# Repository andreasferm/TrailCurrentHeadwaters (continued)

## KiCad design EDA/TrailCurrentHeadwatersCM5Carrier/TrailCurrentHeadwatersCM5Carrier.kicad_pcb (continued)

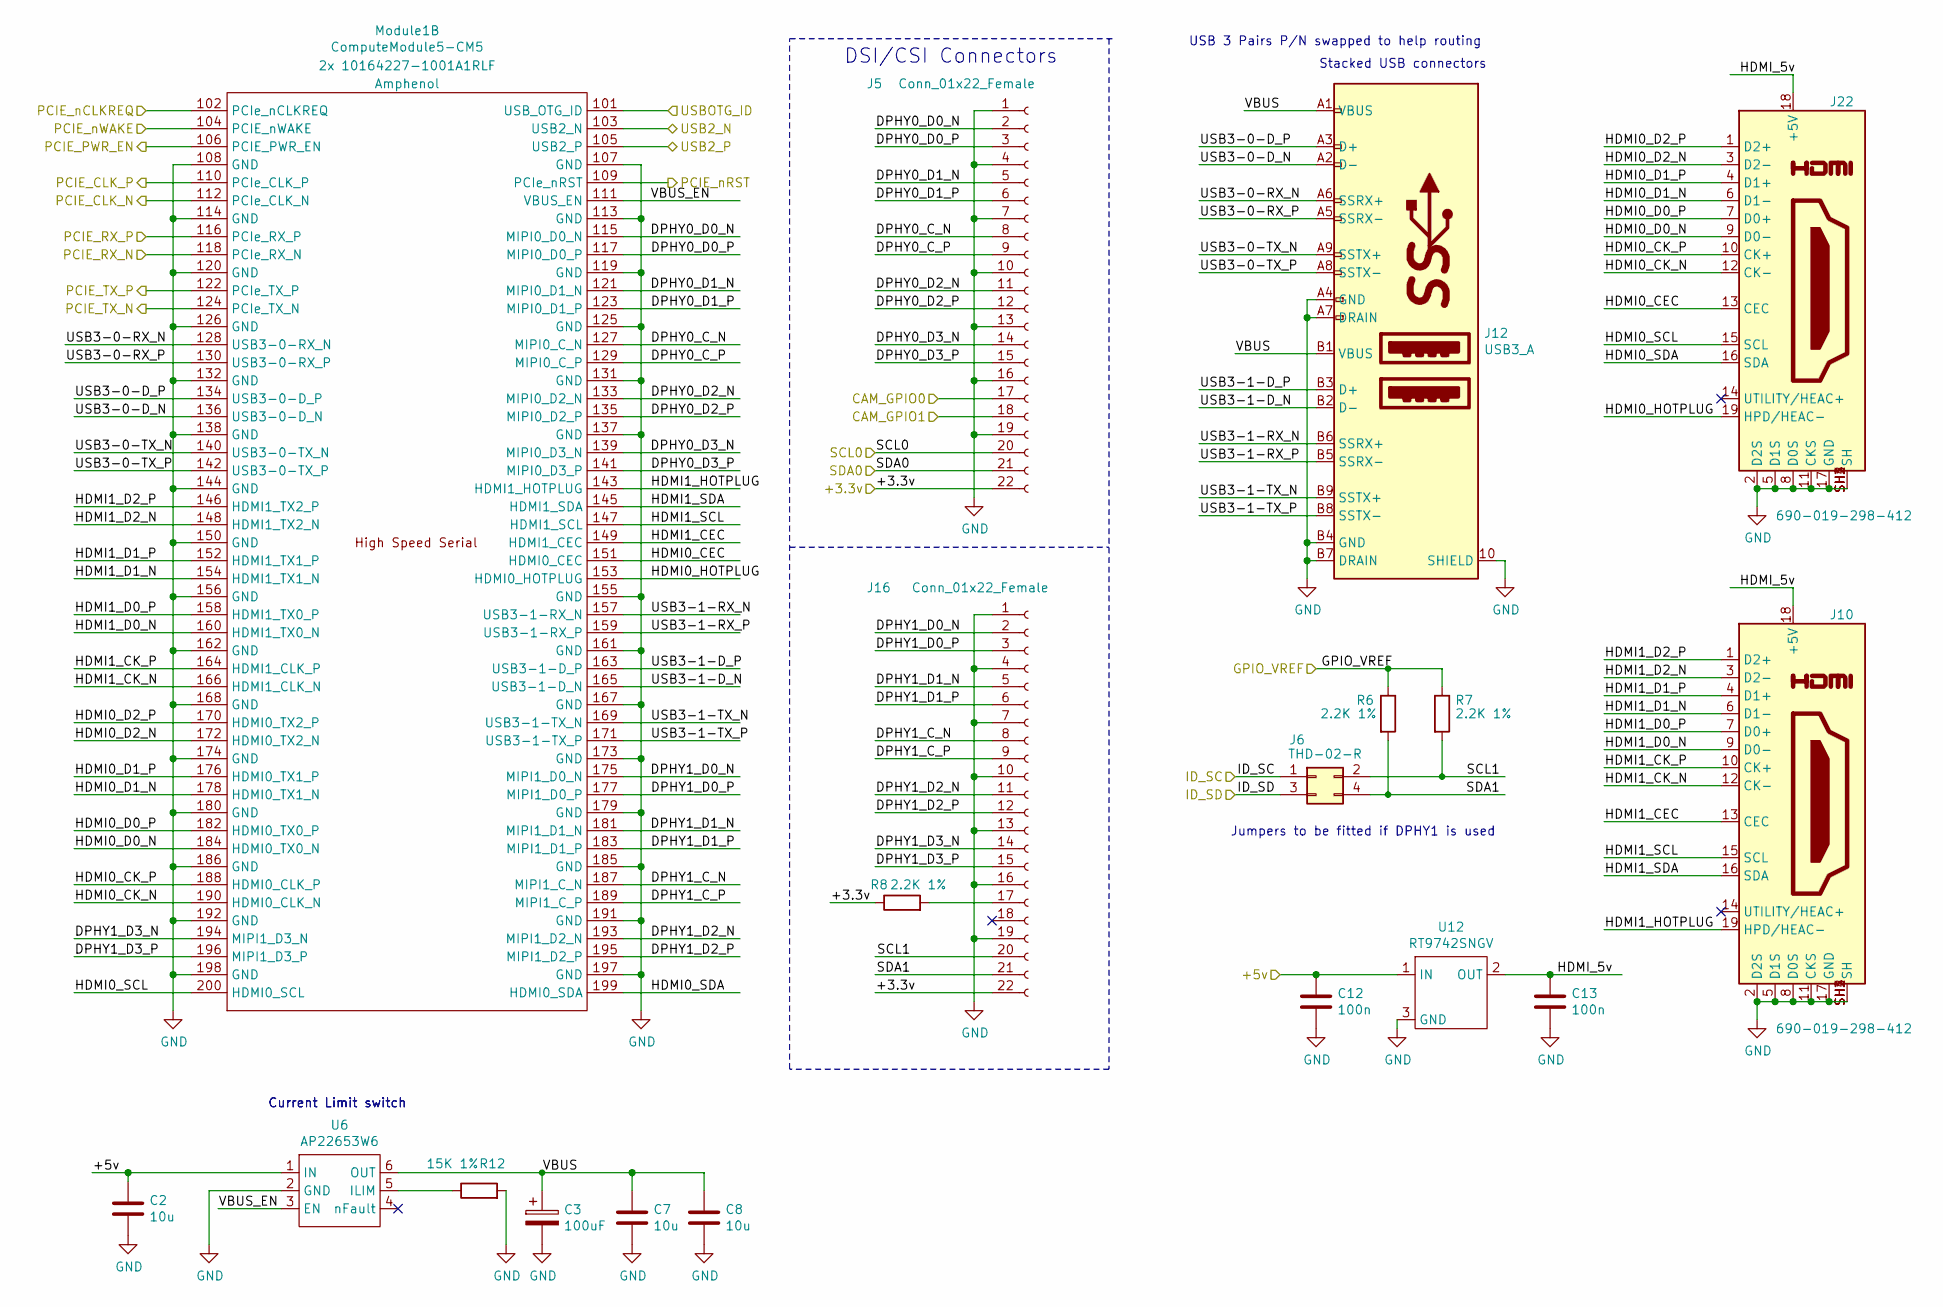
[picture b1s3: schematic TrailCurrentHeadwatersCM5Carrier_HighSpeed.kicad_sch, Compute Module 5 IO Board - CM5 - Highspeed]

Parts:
C2, C7, C8: 10u; C_0805_2012Metric; Part Description 10uF 10% 10V Ceramic Capacitor X7R 0805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
C3: 100uF; CP_EIA-7343-31_Kemet-D; Part Description Capacitor, SP-Cap, 100u, 6.3V, 15mR ESR
C12, C13: 100n; C_0402_1005Metric; Part Description 0.1uF 10% 16V Ceramic Capacitor X7R 040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
J5, J16: Conn_01x22_Female; Hirose_FH12-22S-0.5SH_1x22-1MP_P0.50mm_Horizontal; Part Description 22 Position FFC, FPC Connector Contacts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
J6: THD-02-R; PinHeader_2x02_P2.54mm_Vertical; Part Description PinHeader_2x02_P2.54mm_Vertical
J10, J22: 690-019-298-412; EDAC 690-019-298-412; Part Description HDMI Connector, Right Angle, 19 Contact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
J12: USB3_A; MTCONN_UBAF30-D2011; Part Description Dual USB 3 connector
Module1: ComputeModule5-CM5; Raspberry-Pi-5-Compute-Module; Part Description 100 Position Connector Receptacle, Cent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
R6, R7, R8: 2.2K 1%; R_0402_1005Metric; Part Description Resistor 2.2K M1005 1% 63mW
R12: 15K 1%; R_0402_1005Metric; Part Description Resistor 15K M1005 1% 63mW
U6: AP22653W6; SOT-23-6; Part Description Power Switch/Driver 1:1 P-Channel 2.1A 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
U12: RT9742SNGV; TSOT-23_HandSoldering; Part Description Power Switch/Driver 1:1 N-Channel 500mA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

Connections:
/+3.3v: J5.22, J16.22, R8.1; also elsewhere on the board
/+5v: C2.1, C12.1, U6.1 (IN), U12.1 (IN); also elsewhere on the board
/TrailCurrentHeadwatersCM5Carrier_GPIO/CAM_GPIO0: J5.17; also elsewhere on the board
/TrailCurrentHeadwatersCM5Carrier_GPIO/CAM_GPIO1: J5.18; also elsewhere on the board
/TrailCurrentHeadwatersCM5Carrier_GPIO/GPIO_VREF: R6.1, R7.1; also elsewhere on the board
/TrailCurrentHeadwatersCM5Carrier_GPIO/ID_SC: J6.1; also elsewhere on the board
/TrailCurrentHeadwatersCM5Carrier_GPIO/ID_SD: J6.3; also elsewhere on the board
/TrailCurrentHeadwatersCM5Carrier_GPIO/USBOTG: Module1.101 (USB_OTG_ID); also elsewhere on the board
/TrailCurrentHeadwatersCM5Carrier_HighSpeed/DPHY0_C_N: J5.8, Module1.127 (MIPI0_C_N)
/TrailCurrentHeadwatersCM5Carrier_HighSpeed/DPHY0_C_P: J5.9, Module1.129 (MIPI0_C_P)
/TrailCurrentHeadwatersCM5Carrier_HighSpeed/DPHY0_D0_N: J5.2, Module1.115 (MIPI0_D0_N)
/TrailCurrentHeadwatersCM5Carrier_HighSpeed/DPHY0_D0_P: J5.3, Module1.117 (MIPI0_D0_P)
/TrailCurrentHeadwatersCM5Carrier_HighSpeed/DPHY0_D1_N: J5.5, Module1.121 (MIPI0_D1_N)
/TrailCurrentHeadwatersCM5Carrier_HighSpeed/DPHY0_D1_P: J5.6, Module1.123 (MIPI0_D1_P)
/TrailCurrentHeadwatersCM5Carrier_HighSpeed/DPHY0_D2_N: J5.11, Module1.133 (MIPI0_D2_N)
/TrailCurrentHeadwatersCM5Carrier_HighSpeed/DPHY0_D2_P: J5.12, Module1.135 (MIPI0_D2_P)
/TrailCurrentHeadwatersCM5Carrier_HighSpeed/DPHY0_D3_N: J5.14, Module1.139 (MIPI0_D3_N)
/TrailCurrentHeadwatersCM5Carrier_HighSpeed/DPHY0_D3_P: J5.15, Module1.141 (MIPI0_D3_P)
/TrailCurrentHeadwatersCM5Carrier_HighSpeed/DPHY1_C_N: J16.8, Module1.187 (MIPI1_C_N)
/TrailCurrentHeadwatersCM5Carrier_HighSpeed/DPHY1_C_P: J16.9, Module1.189 (MIPI1_C_P)
/TrailCurrentHeadwatersCM5Carrier_HighSpeed/DPHY1_D0_N: J16.2, Module1.175 (MIPI1_D0_N)
/TrailCurrentHeadwatersCM5Carrier_HighSpeed/DPHY1_D0_P: J16.3, Module1.177 (MIPI1_D0_P)
/TrailCurrentHeadwatersCM5Carrier_HighSpeed/DPHY1_D1_N: J16.5, Module1.181 (MIPI1_D1_N)
/TrailCurrentHeadwatersCM5Carrier_HighSpeed/DPHY1_D1_P: J16.6, Module1.183 (MIPI1_D1_P)
/TrailCurrentHeadwatersCM5Carrier_HighSpeed/DPHY1_D2_N: J16.11, Module1.193 (MIPI1_D2_N)
/TrailCurrentHeadwatersCM5Carrier_HighSpeed/DPHY1_D2_P: J16.12, Module1.195 (MIPI1_D2_P)
/TrailCurrentHeadwatersCM5Carrier_HighSpeed/DPHY1_D3_N: J16.14, Module1.194 (MIPI1_D3_N)
/TrailCurrentHeadwatersCM5Carrier_HighSpeed/DPHY1_D3_P: J16.15, Module1.196 (MIPI1_D3_P)
/TrailCurrentHeadwatersCM5Carrier_HighSpeed/HDMI0_CEC: J22.13 (CEC), Module1.151 (HDMI0_CEC)
/TrailCurrentHeadwatersCM5Carrier_HighSpeed/HDMI0_CK_N: J22.12 (CK-), Module1.190 (HDMI0_CLK_N)
/TrailCurrentHeadwatersCM5Carrier_HighSpeed/HDMI0_CK_P: J22.10 (CK+), Module1.188 (HDMI0_CLK_P)
/TrailCurrentHeadwatersCM5Carrier_HighSpeed/HDMI0_D0_N: J22.9 (D0-), Module1.184 (HDMI0_TX0_N)
/TrailCurrentHeadwatersCM5Carrier_HighSpeed/HDMI0_D0_P: J22.7 (D0+), Module1.182 (HDMI0_TX0_P)
/TrailCurrentHeadwatersCM5Carrier_HighSpeed/HDMI0_D1_N: J22.6 (D1-), Module1.178 (HDMI0_TX1_N)
/TrailCurrentHeadwatersCM5Carrier_HighSpeed/HDMI0_D1_P: J22.4 (D1+), Module1.176 (HDMI0_TX1_P)
/TrailCurrentHeadwatersCM5Carrier_HighSpeed/HDMI0_D2_N: J22.3 (D2-), Module1.172 (HDMI0_TX2_N)
/TrailCurrentHeadwatersCM5Carrier_HighSpeed/HDMI0_D2_P: J22.1 (D2+), Module1.170 (HDMI0_TX2_P)
/TrailCurrentHeadwatersCM5Carrier_HighSpeed/HDMI0_HOTPLUG: J22.19 (HPD/HEAC-), Module1.153 (HDMI0_HOTPLUG)
/TrailCurrentHeadwatersCM5Carrier_HighSpeed/HDMI0_SCL: J22.15 (SCL), Module1.200 (HDMI0_SCL)
/TrailCurrentHeadwatersCM5Carrier_HighSpeed/HDMI0_SDA: J22.16 (SDA), Module1.199 (HDMI0_SDA)
/TrailCurrentHeadwatersCM5Carrier_HighSpeed/HDMI1_CEC: J10.13 (CEC), Module1.149 (HDMI1_CEC)
/TrailCurrentHeadwatersCM5Carrier_HighSpeed/HDMI1_CK_N: J10.12 (CK-), Module1.166 (HDMI1_CLK_N)
/TrailCurrentHeadwatersCM5Carrier_HighSpeed/HDMI1_CK_P: J10.10 (CK+), Module1.164 (HDMI1_CLK_P)
/TrailCurrentHeadwatersCM5Carrier_HighSpeed/HDMI1_D0_N: J10.9 (D0-), Module1.160 (HDMI1_TX0_N)
/TrailCurrentHeadwatersCM5Carrier_HighSpeed/HDMI1_D0_P: J10.7 (D0+), Module1.158 (HDMI1_TX0_P)
/TrailCurrentHeadwatersCM5Carrier_HighSpeed/HDMI1_D1_N: J10.6 (D1-), Module1.154 (HDMI1_TX1_N)
/TrailCurrentHeadwatersCM5Carrier_HighSpeed/HDMI1_D1_P: J10.4 (D1+), Module1.152 (HDMI1_TX1_P)
/TrailCurrentHeadwatersCM5Carrier_HighSpeed/HDMI1_D2_N: J10.3 (D2-), Module1.148 (HDMI1_TX2_N)
/TrailCurrentHeadwatersCM5Carrier_HighSpeed/HDMI1_D2_P: J10.1 (D2+), Module1.146 (HDMI1_TX2_P)
/TrailCurrentHeadwatersCM5Carrier_HighSpeed/HDMI1_HOTPLUG: J10.19 (HPD/HEAC-), Module1.143 (HDMI1_HOTPLUG)
/TrailCurrentHeadwatersCM5Carrier_HighSpeed/HDMI1_SCL: J10.15 (SCL), Module1.147 (HDMI1_SCL)
/TrailCurrentHeadwatersCM5Carrier_HighSpeed/HDMI1_SDA: J10.16 (SDA), Module1.145 (HDMI1_SDA)
/TrailCurrentHeadwatersCM5Carrier_HighSpeed/HDMI_5v: C13.1, J10.18 (+5V), J22.18 (+5V), U12.2 (OUT)
/TrailCurrentHeadwatersCM5Carrier_HighSpeed/PCIE_CLK_N: Module1.112 (PCIe_CLK_N); also elsewhere on the board
/TrailCurrentHeadwatersCM5Carrier_HighSpeed/PCIE_CLK_P: Module1.110 (PCIe_CLK_P); also elsewhere on the board
/TrailCurrentHeadwatersCM5Carrier_HighSpeed/PCIE_PWR_EN: Module1.106 (PCIE_PWR_EN); also elsewhere on the board
/TrailCurrentHeadwatersCM5Carrier_HighSpeed/PCIE_RX_N: Module1.118 (PCIe_RX_N); also elsewhere on the board
/TrailCurrentHeadwatersCM5Carrier_HighSpeed/PCIE_RX_P: Module1.116 (PCIe_RX_P); also elsewhere on the board
/TrailCurrentHeadwatersCM5Carrier_HighSpeed/PCIE_TX_N: Module1.124 (PCIe_TX_N); also elsewhere on the board
/TrailCurrentHeadwatersCM5Carrier_HighSpeed/PCIE_TX_P: Module1.122 (PCIe_TX_P); also elsewhere on the board
/TrailCurrentHeadwatersCM5Carrier_HighSpeed/PCIE_nCLKREQ: Module1.102 (PCIe_nCLKREQ); also elsewhere on the board
/TrailCurrentHeadwatersCM5Carrier_HighSpeed/PCIE_nRST: Module1.109 (PCIe_nRST); also elsewhere on the board
/TrailCurrentHeadwatersCM5Carrier_HighSpeed/PCIE_nWAKE: Module1.104 (PCIE_nWAKE); also elsewhere on the board
/TrailCurrentHeadwatersCM5Carrier_HighSpeed/SCL0: J5.20; also elsewhere on the board
/TrailCurrentHeadwatersCM5Carrier_HighSpeed/SCL1: J6.2, J16.20, R7.2
/TrailCurrentHeadwatersCM5Carrier_HighSpeed/SDA0: J5.21; also elsewhere on the board
/TrailCurrentHeadwatersCM5Carrier_HighSpeed/SDA1: J6.4, J16.21, R6.2
/TrailCurrentHeadwatersCM5Carrier_HighSpeed/USB3-0-D_N: J12.A2 (D-), Module1.136 (USB3-0-D_N)
/TrailCurrentHeadwatersCM5Carrier_HighSpeed/USB3-0-D_P: J12.A3 (D+), Module1.134 (USB3-0-D_P)
/TrailCurrentHeadwatersCM5Carrier_HighSpeed/USB3-0-RX_N: J12.A6 (SSRX+), Module1.128 (USB3-0-RX_N)
/TrailCurrentHeadwatersCM5Carrier_HighSpeed/USB3-0-RX_P: J12.A5 (SSRX-), Module1.130 (USB3-0-RX_P)
/TrailCurrentHeadwatersCM5Carrier_HighSpeed/USB3-0-TX_N: J12.A9 (SSTX+), Module1.140 (USB3-0-TX_N)
/TrailCurrentHeadwatersCM5Carrier_HighSpeed/USB3-0-TX_P: J12.A8 (SSTX-), Module1.142 (USB3-0-TX_P)
/TrailCurrentHeadwatersCM5Carrier_HighSpeed/USB3-1-D_N: J12.B2 (D-), Module1.165 (USB3-1-D_N)
/TrailCurrentHeadwatersCM5Carrier_HighSpeed/USB3-1-D_P: J12.B3 (D+), Module1.163 (USB3-1-D_P)
/TrailCurrentHeadwatersCM5Carrier_HighSpeed/USB3-1-RX_N: J12.B6 (SSRX+), Module1.157 (USB3-1-RX_N)
/TrailCurrentHeadwatersCM5Carrier_HighSpeed/USB3-1-RX_P: J12.B5 (SSRX-), Module1.159 (USB3-1-RX_P)
/TrailCurrentHeadwatersCM5Carrier_HighSpeed/USB3-1-TX_N: J12.B9 (SSTX+), Module1.169 (USB3-1-TX_N)
/TrailCurrentHeadwatersCM5Carrier_HighSpeed/USB3-1-TX_P: J12.B8 (SSTX-), Module1.171 (USB3-1-TX_P)
/TrailCurrentHeadwatersCM5Carrier_HighSpeed/VBUS: C3.1, C7.1, C8.1, J12.A1 (VBUS), J12.B1 (VBUS), U6.6 (OUT)
/TrailCurrentHeadwatersCM5Carrier_HighSpeed/VBUS_EN: Module1.111 (VBUS_EN), U6.3 (EN)
/USB2_N: Module1.103 (USB2_N); also elsewhere on the board
/USB2_P: Module1.105 (USB2_P); also elsewhere on the board
GND: C2.2, C3.2, C7.2, C8.2, C12.2, C13.2, J5.1, J5.4, J5.7, J5.10, J5.13, J5.16, J5.19, J10.2 (D2S), J10.5 (D1S), J10.8 (D0S), J10.11 (CKS), J10.17 (GND), J10.SH1 (SH), J10.SH2 (SH), J10.SH3 (SH), J10.SH4 (SH), J12.10 (SHIELD), J12.A4 (GND), J12.A7 (DRAIN), J12.B4 (GND), J12.B7 (DRAIN), J16.1, J16.4, J16.7, J16.10, J16.13, J16.16, J16.19, J22.2 (D2S), J22.5 (D1S), J22.8 (D0S), J22.11 (CKS), J22.17 (GND), J22.SH1 (SH), J22.SH2 (SH), J22.SH3 (SH), J22.SH4 (SH), Module1.107 (GND), Module1.108 (GND), Module1.113 (GND), Module1.114 (GND), Module1.119 (GND), Module1.120 (GND), Module1.125 (GND), Module1.126 (GND), Module1.131 (GND), Module1.132 (GND), Module1.137 (GND), Module1.138 (GND), Module1.144 (GND), Module1.150 (GND), Module1.155 (GND), Module1.156 (GND), Module1.161 (GND), Module1.162 (GND), Module1.167 (GND), Module1.168 (GND), Module1.173 (GND), Module1.174 (GND), Module1.179 (GND), Module1.180 (GND), Module1.185 (GND), Module1.186 (GND), Module1.191 (GND), Module1.192 (GND), Module1.197 (GND), Module1.198 (GND), R12.2, U6.2 (GND), U12.3 (GND); also elsewhere on the board
unnamed: J16.17, R8.2
unnamed: R12.1, U6.5 (ILIM)

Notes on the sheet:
USB 3 Pairs P/N swapped to help routing
Jumpers to be fitted if DPHY1 is used
Current Limit switch
DSI/CSI Connectors
Stacked USB connectors

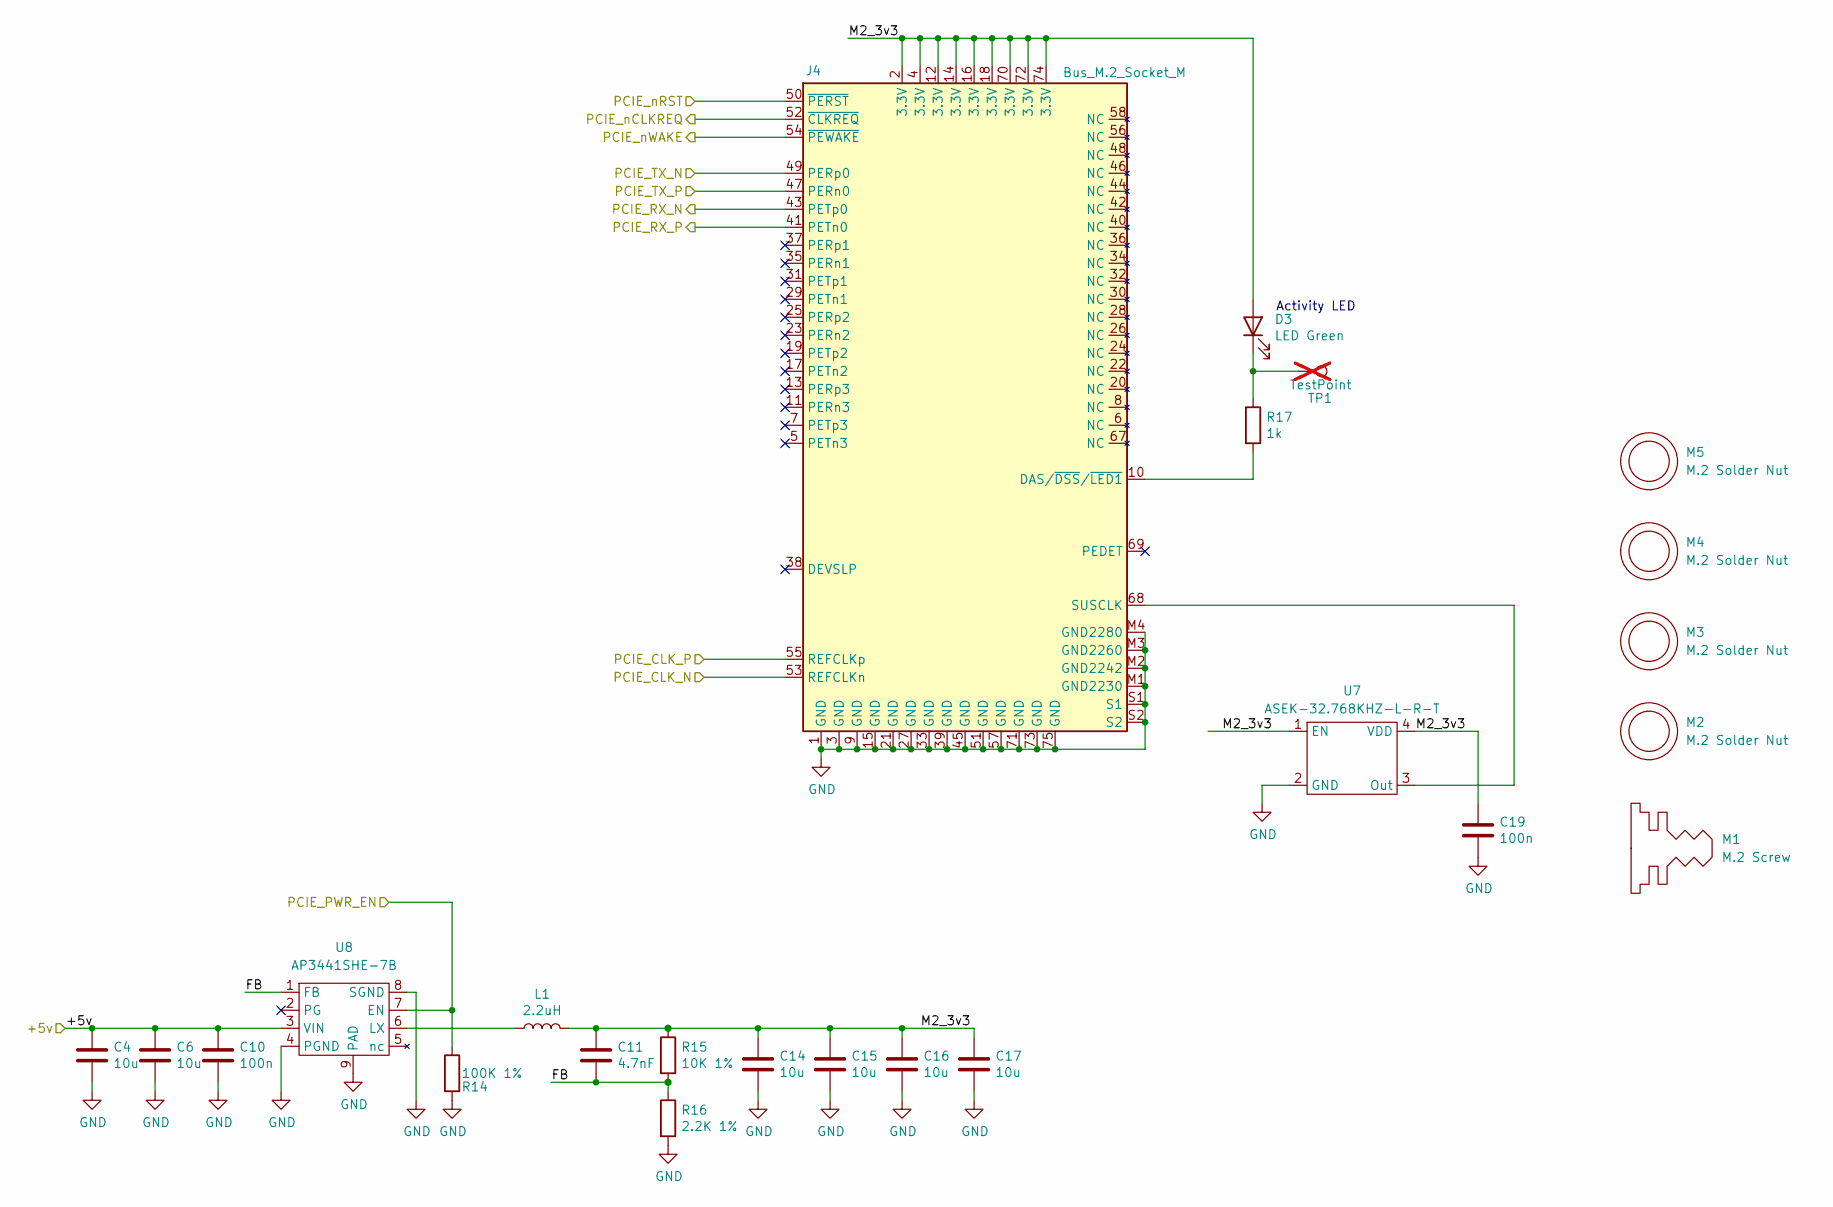
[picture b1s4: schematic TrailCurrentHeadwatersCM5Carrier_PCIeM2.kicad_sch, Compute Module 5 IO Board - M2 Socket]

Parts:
C4, C6, C14, C15, C16, C17: 10u; C_0805_2012Metric; Part Description 10uF 10% 10V Ceramic Capacitor X7R 0805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
C10, C19: 100n; C_0402_1005Metric; Part Description 0.1uF 10% 16V Ceramic Capacitor X7R 040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
C11: 4.7nF; C_0402_1005Metric; Part Description 4.7nF capacitor 0402
D3: LED Green; LED_0603_1608Metric; Part Description Green 572nm LED Indication - Discrete 2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
J4: Bus_M.2_Socket_M; M.2 M Key socket; Part Description M.2 M Key connector
L1: 2.2uH; L_Bourns_SRP5030CC; Part Description Inductor, SMT, 2520, 2u2, IRMS=7A, ISAT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
M1: M.2 Screw; Part Description M.2 Screw
M2, M3, M4, M5: M.2 Solder Nut; Part Description Solder nut for M.2 slot
R14: 100K 1%; R_0402_1005Metric; Part Description Resistor 100K M1005 1% 63mW
R15: 10K 1%; R_0402_1005Metric; Part Description Resistor 10K M1005 1% 63mW
R16: 2.2K 1%; R_0402_1005Metric; Part Description Resistor 2.2K M1005 1% 63mW
R17: 1k; R_0402_1005Metric; Part Description Resistor 1K M1005 1% 63mW
TP1: TestPoint; TestPoint_Pad_2.0x2.0mm; Part Description Test point; not fitted
U7: ASEK-32.768KHZ-L-R-T; Crystal_SMD_3225-4Pin_3.2x2.5mm; Part Description 32KHz Xtal oscilator
U8: AP3441SHE-7B; DFN-8-1EP_2x2mm_P0.5mm_EP1.05x1.75mm; Part Description 3A DC-DC converter

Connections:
/+5v: C4.1, C6.1, C10.1, U8.3 (VIN); also elsewhere on the board
/TrailCurrentHeadwatersCM5Carrier_HighSpeed/PCIE_CLK_N: J4.53 (REFCLKn); also elsewhere on the board
/TrailCurrentHeadwatersCM5Carrier_HighSpeed/PCIE_CLK_P: J4.55 (REFCLKp); also elsewhere on the board
/TrailCurrentHeadwatersCM5Carrier_HighSpeed/PCIE_PWR_EN: R14.1, U8.7 (EN); also elsewhere on the board
/TrailCurrentHeadwatersCM5Carrier_HighSpeed/PCIE_RX_N: J4.43 (PETp0); also elsewhere on the board
/TrailCurrentHeadwatersCM5Carrier_HighSpeed/PCIE_RX_P: J4.41 (PETn0); also elsewhere on the board
/TrailCurrentHeadwatersCM5Carrier_HighSpeed/PCIE_TX_N: J4.49 (PERp0); also elsewhere on the board
/TrailCurrentHeadwatersCM5Carrier_HighSpeed/PCIE_TX_P: J4.47 (PERn0); also elsewhere on the board
/TrailCurrentHeadwatersCM5Carrier_HighSpeed/PCIE_nCLKREQ: J4.52 (~CLKREQ); also elsewhere on the board
/TrailCurrentHeadwatersCM5Carrier_HighSpeed/PCIE_nRST: J4.50 (~PERST); also elsewhere on the board
/TrailCurrentHeadwatersCM5Carrier_HighSpeed/PCIE_nWAKE: J4.54 (~PEWAKE); also elsewhere on the board
/TrailCurrentHeadwatersCM5Carrier_PCIeM2/FB: C11.2, R15.2, R16.1, U8.1 (FB)
/TrailCurrentHeadwatersCM5Carrier_PCIeM2/M2_3v3: C11.1, C14.1, C15.1, C16.1, C17.1, C19.1, D3.2 (A), J4.2 (3.3V), J4.4 (3.3V), J4.12 (3.3V), J4.14 (3.3V), J4.16 (3.3V), J4.18 (3.3V), J4.70 (3.3V), J4.72 (3.3V), J4.74 (3.3V), L1.2, R15.1, U7.1 (EN), U7.4 (VDD)
GND: C4.2, C6.2, C10.2, C14.2, C15.2, C16.2, C17.2, C19.2, J4.1 (GND), J4.3 (GND), J4.9 (GND), J4.15 (GND), J4.21 (GND), J4.27 (GND), J4.33 (GND), J4.39 (GND), J4.45 (GND), J4.51 (GND), J4.57 (GND), J4.71 (GND), J4.73 (GND), J4.75 (GND), J4.M1 (GND2230), J4.M2 (GND2242), J4.M3 (GND2260), J4.M4 (GND2280), J4.S1, J4.S2, R14.2, R16.2, U7.2 (GND), U8.4 (PGND), U8.8 (SGND), U8.9 (PAD); also elsewhere on the board
unnamed: D3.1 (K), R17.1, TP1.1
unnamed: J4.10 (DAS/~DSS/~LED1), R17.2
unnamed: J4.68 (SUSCLK), U7.3 (Out)
unnamed: L1.1, U8.6 (LX)

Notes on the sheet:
Activity LED

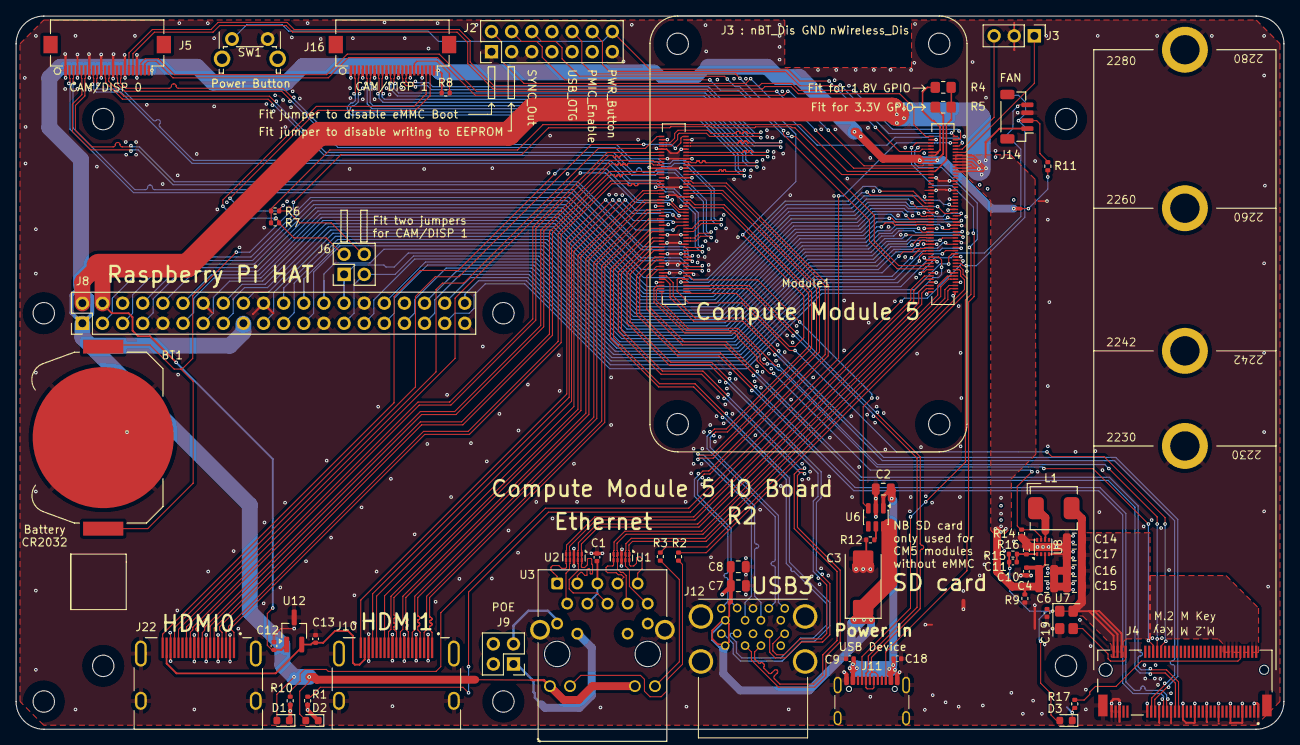
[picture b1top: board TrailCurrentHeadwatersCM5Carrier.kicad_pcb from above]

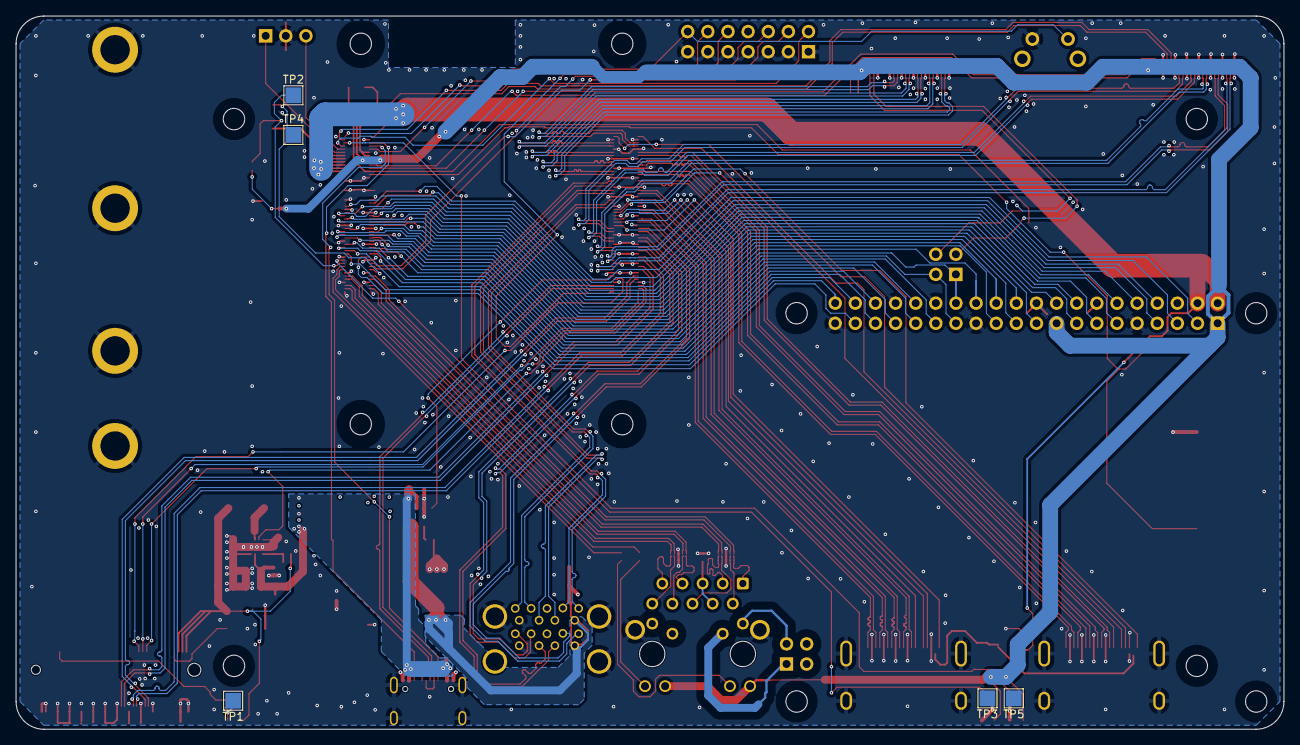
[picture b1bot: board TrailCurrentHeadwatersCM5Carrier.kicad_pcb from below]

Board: 4 copper layers, 160.0 x 90.0 mm, 74 parts (5 on the bottom side), 152 nets.

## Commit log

2026-03-15 Fixed data being persisted to db when it shoudl come directrly from MQTT. Also updated deployment to update node-red flow versions
2026-03-15 Updates to allow for calibration data, updates to ensure node-red workflows get updated.
2026-03-15 Additional updates to push config changes to the cloud
2026-03-15 Fixed snapshot missing relay property
2026-03-15 Updated name and icon to help distinguish between local and cloud
2026-03-15 Updated workflow to fix Plateau from not sending data
2026-03-15 Fixing position of nodes in the node-red workflows
2026-03-16 Added icons for all devices and fixed bug with sync of config to cloud
2026-03-16 Fix to deployment package for replacing SHA correctly after name change
2026-03-19 Adding enclosure image
2026-03-21 CM5 Module image creation and WIP for case design for CM5 Development Kit.
2026-03-21 Bringing in CM5 devkit board as starting point
2026-03-21 Carrier board updated to point to items brought into our own libraries
2026-03-21 Working through warnings to cleanup schematic
2026-03-21 CM5 script updated to ignore eMMC. NVME is needed anyway for the tileserver and this allows for cheaper CM5 modules to be used. CM5 modules with eMMC can still be used just unfortunately it will be $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
2026-03-21 Updated instructions and fixes to image build
2026-03-22 Fixes for SSL cert generation and progress on new Case design
2026-03-22 Adding logo and splash screen to image. Updates to the CM5 case design
2026-03-22 Fixed bug where modules are getting added multiple times. Progress on Pi case
2026-03-22 Progress on Headwaters case design
2026-03-22 Changes for plateau to allow for calibration and leveling
2026-03-22 Improvements to the leveling calibration
2026-03-25 Updated image to contain ascii art so when you login you see exactly which TrailCurrent device your connected to.
2026-03-25 Added configuration for sending notiificiations via SMS on the Cellular enabled router
2026-03-26 Removing support for Raspberry Pi5 and replacing with CM5. Allows for easier setup, cheaper cost and all off the shelf components
2026-03-26 Removing EDA now that all items are off the shelf
2026-03-26 Progress on CM5 case design, project updated to have 8 channels for switchback
2026-03-26 Updated PWA to make buttons for Torrent dynamic based on whether the module is configured or not
2026-03-26 Fixing module naming conventions
2026-03-27 Initial device discovery working
2026-03-27 Moved everything into CM5 image with one time script to ensure full app is up and running. Fixed numerous bugs found during device discovery testing. Font and styling fixes too.
2026-03-27 Removing node-red to reduce complexity. First login script now walks user through setup. Initial CM5 image contains NA map data by default. This produces and image ready to run and discover devices, 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
2026-03-28 Removing espota since we moved to ESP-IDF an endpoint will be used for firmware updates
2026-03-28 Clarifying directory change in setup
2026-03-29 Fixes for WiFi credential transfer and more resiliancy for the discovery process
2026-03-29 Updating OTA after move to ESP-IDF
2026-03-29 OTA Changes to algin with ESP-IDF firmware and reporting their version number after an update
2026-03-30 More changes for discovery and versioning. New code added to handle a second switchback node and automatically add more light buttons and use the correct toggle and status IDs for the second instance
2026-03-30 Fixing bug for updating device firmware version on zip or OTA
2026-03-31 Updated to enable active cooling.
2026-04-01 Fixing sudo issue in CM5 build which impacted OTA. Service worker changes so the app can refresh. Notifications added via SMS
2026-04-01 Updated documentation for sudo issues
2026-04-01 Changed QoS priority for cloud for less delay
2026-04-01 Fixed bug with power consumption not reporting correctly
2026-04-02 Adding system stats both to Overlook and sending to Farwatch too
2026-04-03 Proximity rules added
2026-04-03 Updated documentation for proximity rules
2026-04-05 Adding product image and fixing bug with Farwatch not triggering lights
2026-04-05 Fixing bug with speed display
2026-04-08 Setting map to track vehicle
2026-04-08 Changes to manage throughput to the cloud to reduce data usage. State changes monitored and only synced when changes occur or 20s in case messages got missed.
2026-04-08 Updated documentation
2026-04-12 Handling address variants for Switchback, Torrent, and Picket
2026-04-12 Added therma items to devices list for fetching firmware
2026-04-12 Added reservoir to PWA populated data
2026-04-12 Adding zip deployment through the PWA
2026-04-12 Added pattern for discovery and OTA for wireless devices the first was fireside
2026-04-12 Responding to requests from Peregrine for config info
2026-04-13 Fixes for relay commands not being processed
2026-04-15 Fixed bugs with mounts required for PWA deployment both in the image and the deploy script
2026-04-19 Added image build for Radxa variant of headwaters
2026-04-19 Fixed crystal value in base Radxa image for planned wavesahre CAN Hat that will be used
2026-04-20 Adding schematic for HAT and updated build to clean items before build
2026-05-03 Fixes for build of RADXA with waveshare HAT
2026-05-03 Documentation updates
2026-05-05 Fixes for more robust CAN recovery and progress made on Radxa case design
2026-05-06 More CAD work on Radxa Variant
2026-05-07 Case design completed for Radxa variant with 2 color 3d print setup
2026-05-11 Updates for playbill remote
2026-05-13 Changes for playbill remote and warnging about radxa variant
2026-05-15 Fixed config bug trying to set CAN ID of devices which gets set during firmware flashing
2026-05-15 Added time server with GNSS sync
2026-05-16 Playbill refinements
2026-05-17 Peregrine added to Overlook and PWA update fix when added to home screen. No longer have to delete and readd to home screen
2026-05-21 Fix excessive logging when not in debug mode
2026-05-21 Fix for websocket disconnects
2026-05-21 New strategy to reduce frequency of button label changes to reduce traffic on CAN and MQTT
2026-05-21 Removed throttling of CPU
2026-06-09 Removing older files that are no longer used by designs
2026-06-09 Fix Step 6.1 self-SIGTERM that prevented firmware OTA via cloud/PWA deploys
2026-06-09 Added comments
2026-06-15 Freecad file for a case made from sheet metal for cnc milling. Unfolded objects exists in the freecad file. This file is untested
2026-06-15 changing the required tools from qemu-aarch64-static to qemu-aarch64 since that is what is available from apt
2026-06-15 Added support for Australis with CAN IDs 0x030 and 0x031 moving the ones from Plateu to 0xx037 and 0x039, since they are supposed to have moved from the ones i've taken for Australis
2026-06-15 Adding support in the frontend for Australis
2026-06-15 Updating README.md to explain what this is
2026-06-16 Forgot to commit the australis.js page
